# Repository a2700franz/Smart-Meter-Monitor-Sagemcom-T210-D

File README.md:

# Smart Meter Monitor
M-Bus Adapter für Smart Meter Sagemcom T210-D der Netz-NOE mit galvanischer Trennung und Übertragung der Daten ins WLAN.

ACHTUNG: Alle hier eingestellten Informationen erfolgen ohne Gewähr. Dies ist keine Nachbauanleitung, sonder beschreibt lediglich wie ich an diese Projekt herangegangen bin.

Der M-Bus Adapter nutzt die Tatsache, dass das Smart Meter keine Eingaben erfordert. Dadurch genügt die einfache Ansteuerung eines Optokopplers. Die M-Bus Leitungen müssen polrichtig angeschlossen werden. Eine Vertauschung ist unkritisch, ergibt jedoch keine Funktion.

Um ein sauberes Signal sicherzustellen wird ein Schmitt-Trigger benutzt. Die überzähligen Gatter können mittels Jumper für eine Ledanzeige genutzt werden.

Der Optokoppler benötigt eine Stromversorgung zwischen 3V3 und 5V. Der Pegel des Ausgangssignals liegt dann ebenfalls in diesem Bereich.

Der M-Bus Transmitter ist getrennt vom Adapter aufgebaut und dient zur drahtlosen Übertragung der Daten. Es kann hier jeder ESP benutzt werden, die Platine ist für einen ESP-12F ausgelegt, der sich gerade in der Bastelkiste befand. Auf der Platine wurden auch zwei Schalter integriert um sie auch zum Flashen des ESP verwenden zu können.

Die Schalpläne und Platinen wurden mit Eagle gezeichnet.

Die Software für den Transmitter wurde mit der Arduino IDE erstellt. Die Daten werden von der M-Bus Schnittstelle entgegengenommen und mittels UDP an eine beliebige Zieladresse im WLAN weitergeleitet. Wenn kein WLAN gefunden wird startet der der Transmitter als AccessPoint (IP: 192.168.4.1). Die Konfiguration kan dann über ein Webinterface eingestellt werden. Die Software unterstützt OTA und Debugging über UDP.

Die Daten werden bei mir von einem Raspberry 3B zur Decodierung und Aufbereitung entgegengenommen. Ein entsprechendes Python-Programm liegt als Beispiel bei.

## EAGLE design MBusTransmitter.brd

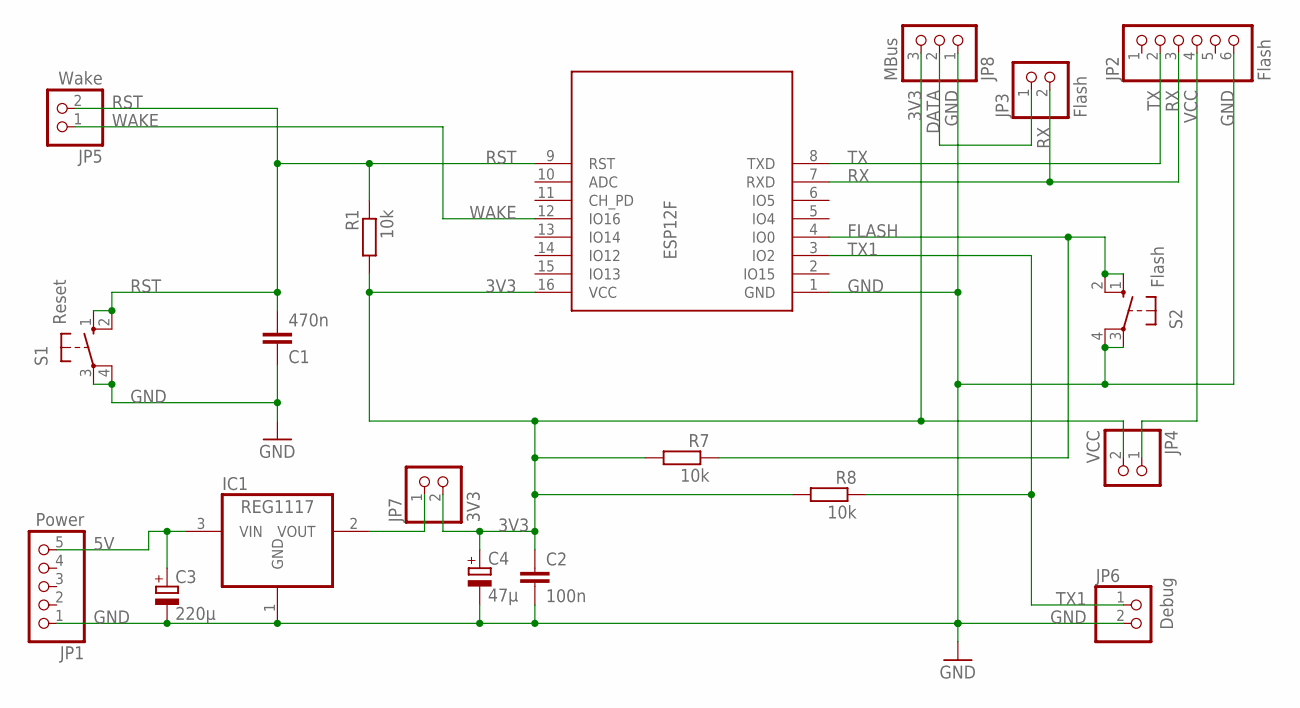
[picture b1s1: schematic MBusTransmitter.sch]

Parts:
C1: 470n; C050-024X044
C2: 100n; C050-024X044
C3: 220µ; E5-10,5
C4: 47µ; E2,5-5
IC1: REG1117; SOT223
JP1: Power; 1X05
JP2: Flash; 1X06
JP3: Flash; 1X02
JP4: VCC; 1X02
JP5: Wake; 1X02
JP6: Debug; 1X02
JP7: 3V3; 1X02
JP8: MBus; 1X03/90
R1, R7, R8: 10k; 0207/10
S1: Reset; B3F-10XX
S2: Flash; B3F-10XX
U$2: ESP12F

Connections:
3V3: C2.1, C4.+, JP4.2, JP7.2, JP8.3, R1.2, R7.2, R8.2, U$2.16 (VCC)
5V: C3.+, IC1.3 (VIN), JP1.5
DATA: JP3.1, JP8.2
FLASH: R7.1, S2.1 (S), S2.2 (S1), U$2.4 (IO0)
GND: C1.1, C2.2, C3.-, C4.-, IC1.1 (GND), JP1.1, JP2.6, JP6.2, JP8.1, S1.3, S1.4 (P1), S2.3, S2.4 (P1), U$2.1 (GND)
unnamed: IC1.2 (VOUT), JP7.1
RST: C1.2, JP5.2, R1.1, S1.1 (S), S1.2 (S1), U$2.9 (RST)
RX: JP2.3, JP3.2, U$2.7 (RXD)
TX: JP2.2, U$2.8 (TXD)
TX1: JP6.1, R8.1, U$2.3 (IO2)
VCC: JP2.4, JP4.1
WAKE: JP5.1, U$2.12 (IO16)

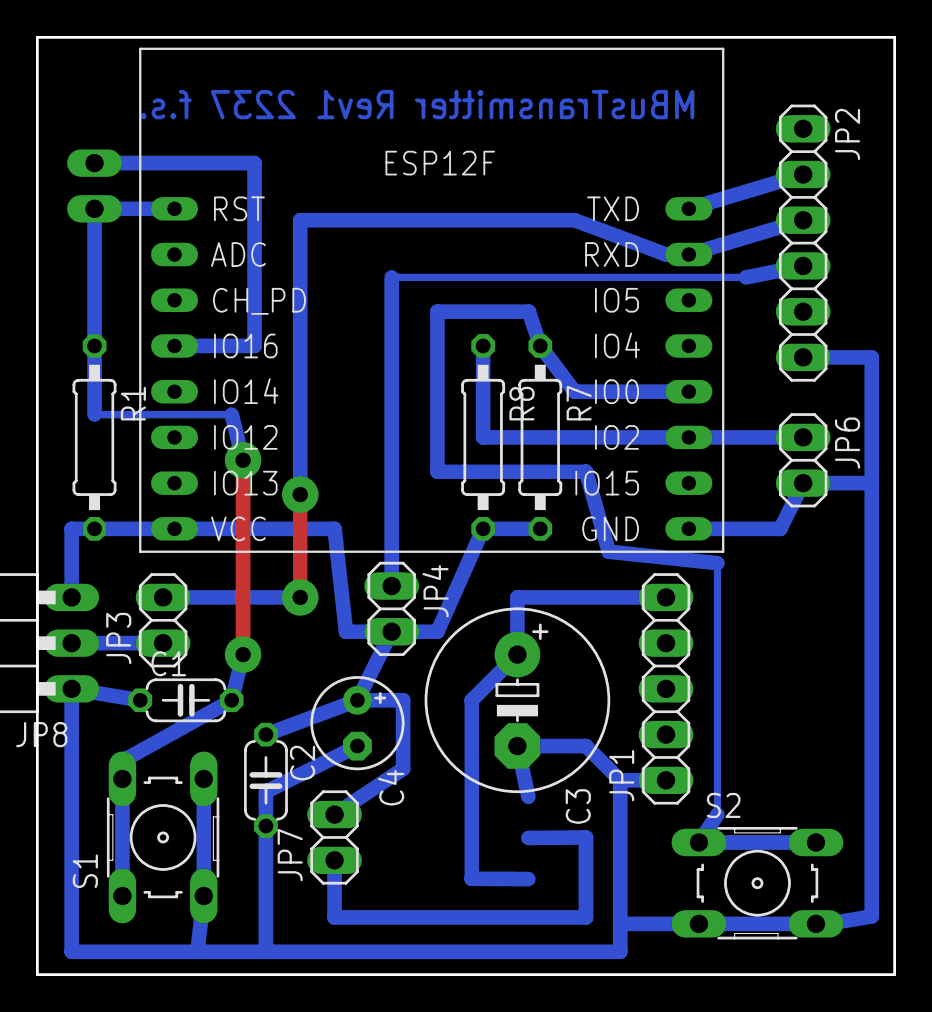
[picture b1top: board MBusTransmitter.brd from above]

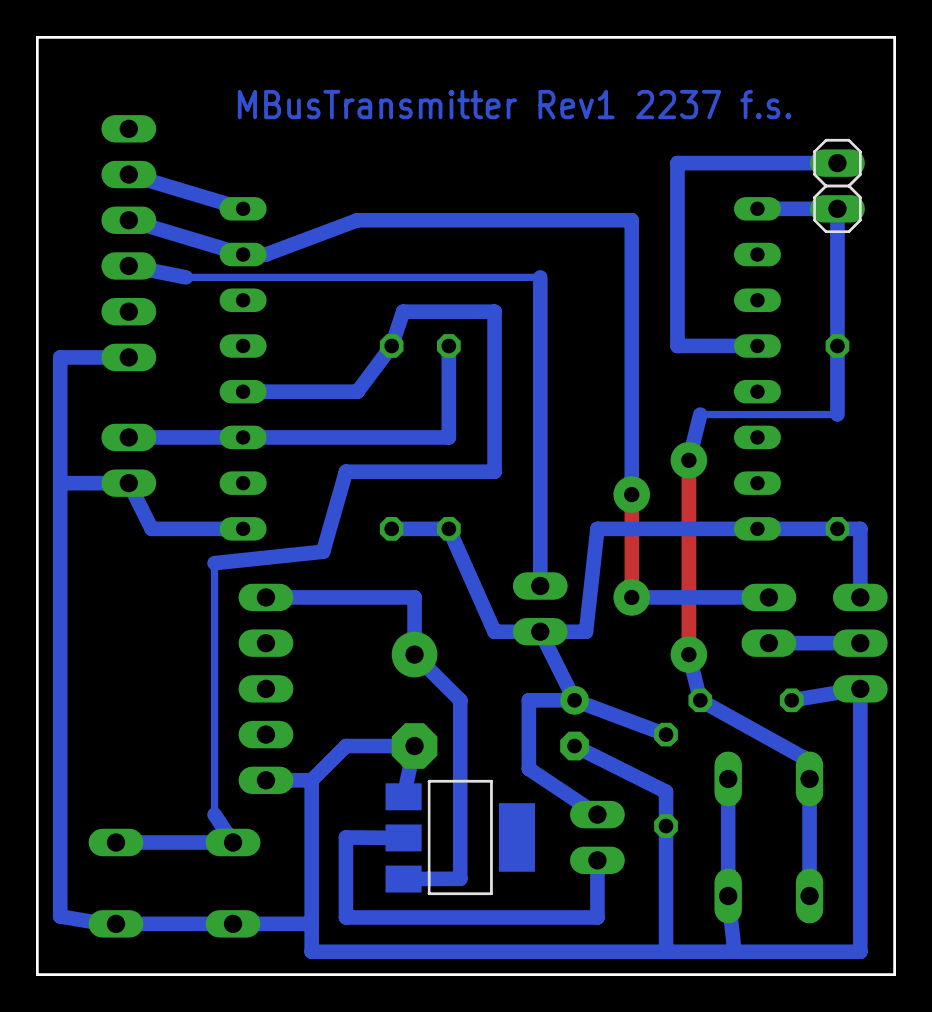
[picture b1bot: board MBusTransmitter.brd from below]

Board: 2 copper layers, 47.6 x 52.1 mm, 19 parts (2 on the bottom side), 12 nets.

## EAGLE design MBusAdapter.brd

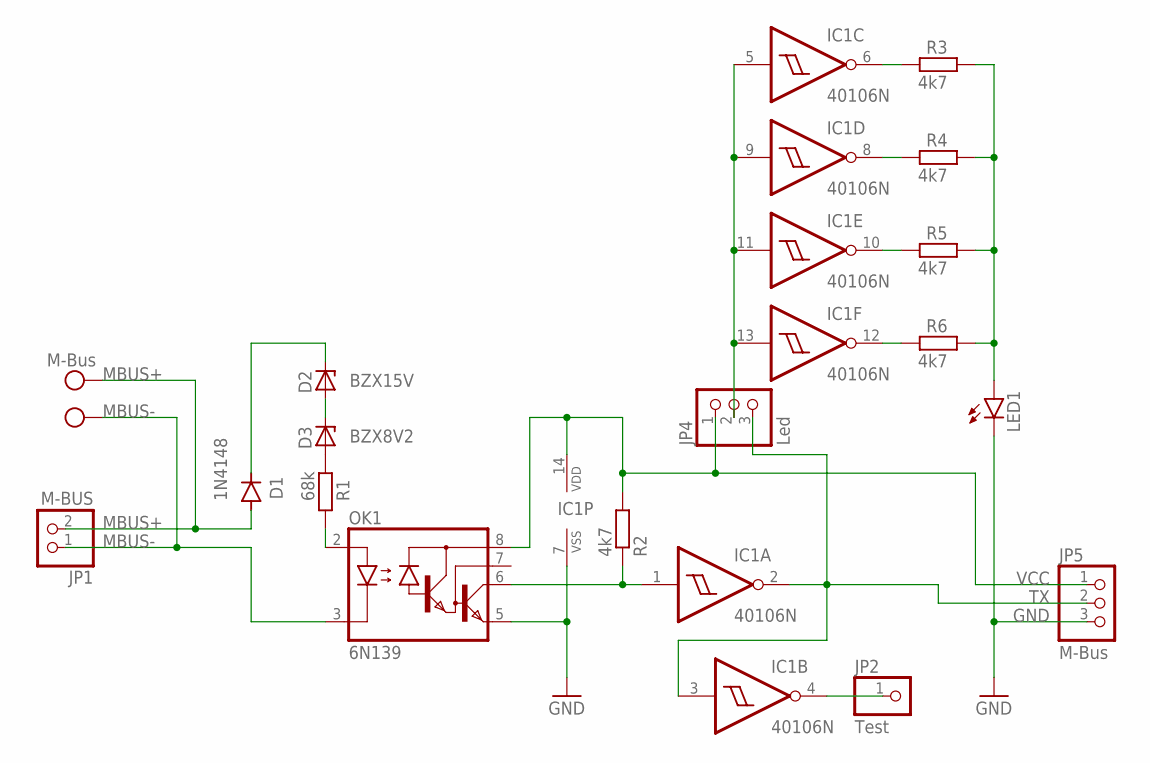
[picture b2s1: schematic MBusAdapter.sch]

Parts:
D1: 1N4148; DO35-10
D2: BZX15V; DO34Z7
D3: BZX8V2; DO34Z7
IC1: 40106N; DIL14
JP1: M-BUS; 1X02
JP2: Test; 1X01
JP4: Led; 1X03
JP5: M-Bus; 1X03
LED1: TLLG4400; LED3MM
M-BUS: M-Bus; W237-102
OK1: 6N139; DIL08
R1: 68k; 0207/10
R2, R3, R4, R5, R6: 4k7; 0207/10

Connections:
GND: IC1.7 (VSS), JP5.3, LED1.K (C), OK1.5 (GND)
MBUS+: D1.A, JP1.2, M-BUS.2
MBUS-: JP1.1, M-BUS.1, OK1.3 (C)
unnamed: D1.C, D2.C
unnamed: D2.A, D3.C
unnamed: D3.A, R1.2
unnamed: OK1.2 (A), R1.1
unnamed: IC1.6 (O), R3.2
unnamed: IC1.1 (I), OK1.6 (VO), R2.1
unnamed: IC1.8 (O), R4.2
unnamed: IC1.10 (O), R5.2
unnamed: IC1.12 (O), R6.2
unnamed: LED1.A, R3.1, R4.1, R5.1, R6.1
unnamed: IC1.5 (I), IC1.9 (I), IC1.11 (I), IC1.13 (I), JP4.2
unnamed: IC1.4 (O), JP2.1
TX: IC1.2 (O), IC1.3 (I), JP4.3, JP5.2
VCC: IC1.14 (VDD), JP4.1, JP5.1, OK1.8 (VCC), R2.2

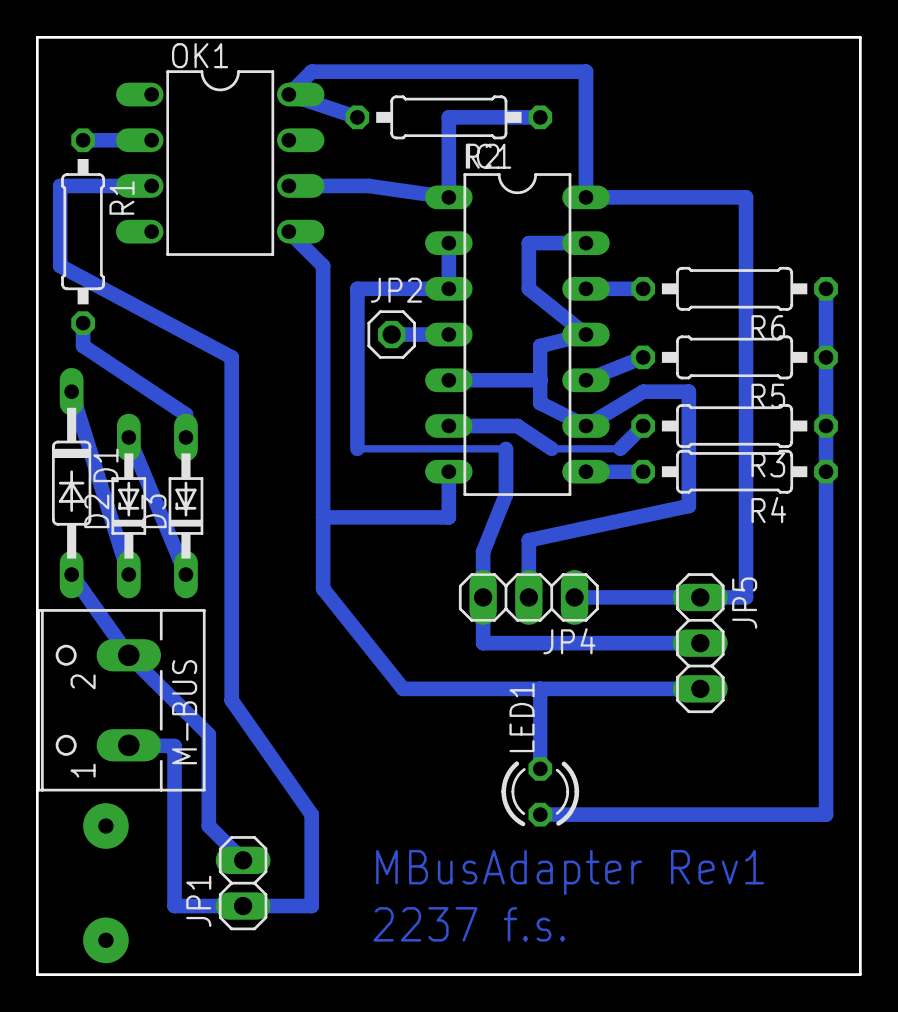
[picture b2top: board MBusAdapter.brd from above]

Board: 2 copper layers, 45.7 x 52.1 mm, 17 parts (0 on the bottom side), 17 nets.
